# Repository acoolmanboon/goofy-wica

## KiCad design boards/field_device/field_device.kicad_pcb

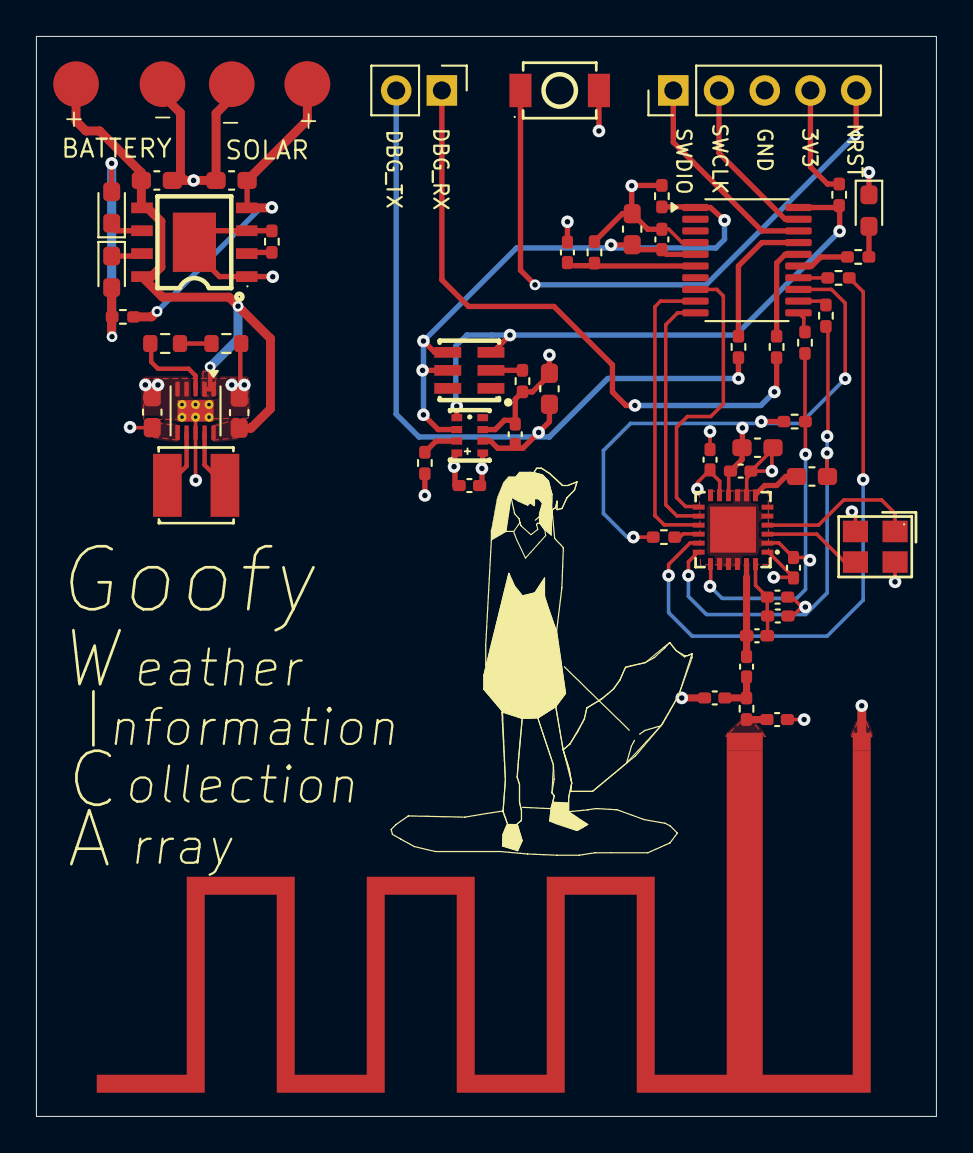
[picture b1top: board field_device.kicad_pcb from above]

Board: 4 copper layers, 50.0 x 60.0 mm, 56 parts (0 on the bottom side), 42 nets.

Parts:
AE1: Antenna; TI DN023 868-955MHz Antenna
BT1: Battery; battery_2_smd
C1, C3, C7, C8, C9, C13: 10uF; C_0603_1608Metric_Pad1.08x0.95mm_HandSolder
C2, C4, C5, C6, C14, C15, C16: 100nF; C_0402_1005Metric_Pad0.74x0.62mm_HandSolder
C10: 22uF; C_0603_1608Metric_Pad1.08x0.95mm_HandSolder
C17: 470nF; C_0603_1608Metric_Pad1.08x0.95mm_HandSolder
C18: 47nF; C_0402_1005Metric_Pad0.74x0.62mm_HandSolder
C19, C20: 100pF; C_0402_1005Metric_Pad0.74x0.62mm_HandSolder
C21: C_Shunt_1; C_0402_1005Metric_Pad0.74x0.62mm_HandSolder
C22: C_Shunt_2; C_0402_1005Metric_Pad0.74x0.62mm_HandSolder
D1, D2, D3: KT-0603R; LED_0603_1608Metric_Pad1.05x0.95mm_HandSolder
J1: PinHeader_1x05_P2.54mm_Vertical
J2: PinHeader_1x02_P2.54mm_Vertical
L1: CR4018-2R2M; IND-SMD_L4.0-W4.0
L2: 47nH; L_0402_1005Metric_Pad0.77x0.64mm_HandSolder
R1: 330R; R_0402_1005Metric_Pad0.72x0.64mm_HandSolder
R2, R3, R4, R11, R12, R13: 10k; R_0402_1005Metric_Pad0.72x0.64mm_HandSolder
R5, R6, R7, R8: 22R; R_0402_1005Metric_Pad0.72x0.64mm_HandSolder
R9, R10, R14, R15: 1k; R_0402_1005Metric_Pad0.72x0.64mm_HandSolder
R16: 0603WAF3302T5E; R_0603_1608Metric
R17: 0; R_0402_1005Metric_Pad0.72x0.64mm_HandSolder
R18: 0603WAF3601T5E; R_0603_1608Metric
SC1: Solar_Cell; battery_2_smd
SW1: TS-1088-AR02016; SW-SMD_L3.9-W3.0-P4.45
U1: CHT20MEMS; LGA-6_L3.0-W3.0-P1.00-BR
U2: STM32C051F8P6; TSSOP-20_4.4x6.5mm_P0.65mm
U3: SPA06-003; LGA-8_L2.5-W2.0-P0.65_SPA06-003
U4: CN3163; ESOP-8_L4.9-W3.9-P1.27-LS6.0-BL-EP
U6: SX1262IMLTRT; QFN-24_L4.0-W4.0-P0.50-BL-EP2.6
U7: TPS63900; WSON-10-1EP_2.5x2.5mm_P0.5mm_EP1.2x2mm_ThermalVias
Y1: X322532MMB4SI; CRYSTAL-SMD_4P-L3.2-W2.5-BL

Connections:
+3.3V: C1.1, C3.1, C4.1, C5.1, C6.1, C10.1, C13.1, C14.1, C15.1, C16.1, J1.4, R1.1, R2.2, R3.2, R4.1, R12.2, R13.1, U2.4 (VDD), U3.6 (VDDIO), U3.8 (VDD), U6.1 (VDD_IN), U6.10 (VBAT), U6.11 (VBAT_IO), U7.6 (VOUT)
/MCU/LOG_MCU_RX: R10.1, U2.17 (PA10/PA12)
/MCU/LOG_MCU_RX_DEBUGGER_TX: J2.2, R10.2
/MCU/LOG_MCU_TX: R9.1, U2.16 (PA9/PA11)
/MCU/LOG_MCU_TX_DEBUGGER_RX: J2.1, R9.2
/MCU/MCU_MISO: R7.1, U2.13 (PA6)
/MCU/MCU_MOSI: R8.1, U2.14 (PA7)
/MCU/MCU_NSS: R5.1, U2.11 (PA4)
/MCU/MCU_SCK: R6.1, U2.12 (PA5)
/MCU/NRST: C2.1, J1.5, R4.2, SW1.2 (B), U2.6 (PF2)
/MCU/RF_BUSY: U2.10 (PA3), U6.14 (BUSY)
/MCU/RF_DIO1: U2.8 (PA1), U6.13 (DIO1)
/MCU/RF_MISO: R7.2, U6.16 (MISO)
/MCU/RF_MOSI: R8.2, U6.17 (MOSI)
/MCU/RF_NRST: U2.9 (PA2), U6.15 (NRESET)
/MCU/RF_NSS: R5.2, R12.1, U6.19 (NSS)
/MCU/RF_SCK: R6.2, U6.18 (SCK)
/MCU/SCL_bus: R3.1, U1.3 (SCL), U2.20 (PB6), U3.4 (SCK)
/MCU/SDA_bus: R2.1, U1.4 (SDA), U2.1 (PB7), U3.3 (SDA)
/MCU/STATUS_LED: R11.1, U2.15 (PA8)
/MCU/SWDCLK: J1.2, U2.19 (PA14)
/MCU/SWDIO: J1.1, U2.18 (PA13)
/lora_module/XTA: U6.3 (XTA), Y1.3
/lora_module/XTB: U6.4 (XTB), Y1.1
/power_source/chrg: D2.1 (K), U4.7 (CHRG#)
/power_source/done: D3.1 (K), U4.6 (DONE#)
/power_source/regulator/CFG1: R18.1, U7.3 (CFG1)
/power_source/regulator/LX1: L1.2, U7.9 (LX1)
/power_source/regulator/LX2: L1.1, U7.7 (LX2)
/power_source/regulator/Vin: BT1.1 (+), C8.1, C9.1, U4.5 (BAT), U4.8 (FB), U7.1 (EN), U7.2 (SEL), U7.10 (VIN)
/power_source/solar_pwr: C7.1, R15.1, SC1.1 (+), U4.4 (VIN)
GND: AE1.1 (A_1), BT1.2 (-), C1.2, C2.2, C3.2, C4.2, C5.2, C6.2, C7.2, C8.2, C9.2, C10.2, C13.2, C14.2, C15.2, C16.2, C17.2, C18.2, C19.2, C21.2, C22.1, C22.2, D1.1 (K), J1.3, R14.2, R16.2, R17.2, SC1.2 (-), SW1.1 (A), U1.5 (VSS), U2.5 (VSS), U3.1 (GND), U3.7 (GND), U4.1 (TEMP), U4.3 (GND), U4.9 (PAD), U6.2 (GND), U6.5 (GND), U6.8 (GND), U6.9 (DCC_SW), U6.20 (GND), U6.21 (RFI_P), U6.22 (RFI_N), U6.25 (GND), U7.4 (CFG2), U7.5 (CFG3), U7.8 (GND), U7.11 (GND), Y1.2 (G), Y1.4 (G)
unnamed: C20.1, C21.1, R17.1
unnamed: D1.2 (A), R11.2
unnamed: D2.2 (A), D3.2 (A), R15.2
unnamed: R16.1, R18.2
unnamed: R1.2, U1.2 (VDD)
unnamed: R13.2, U3.2 (CSB)
unnamed: R14.1, U4.2 (ISET)
unnamed: C20.2, L2.2, U6.23 (RFO)
unnamed: C17.1, U6.7 (VREG)
unnamed: C18.1, C19.1, L2.1, U6.24 (VR_PA)
